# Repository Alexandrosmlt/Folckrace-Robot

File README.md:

# Folckrace Robot

## 1. Project Overview

#### This is an autonomous robot made for Folkrace (which is a robot competition centered around autonomous racing and steering skills). My design features 4 HS DC Motors paired with 5 ToF sensors, providing precise feedback in real time.

## 1.1 Why i am building this project

#### I am making this project to get real-life experience in developing complex systems and working with fast robotics controls. This project is great to help me improve my skills in putting together microcontrollers, motor drivers and sensors in order to create a autonomous and competitive robot.

## 2. Hardware and Design

### 2.1 3D Visualization

* **Front View**:

* **Rear View**:

* **Right View**:

* **Left View**:

* **Final View**:

### 2.2 Custom PCB 

* **PCB Top View**:

* **PCB Bottom View**:

* **PCB Schematic**:

### 2.3 Wiring Diagram

* **Wiring diagram**:

### 2.4 Pinout

#### 1. ToF Sensor Connections (5 Sensors)

>| Component | Function | ESP32 Pin |
>| :--- | :--- | :--- |
>| **I2C Bus** | Data Line (SDA) | **GPIO 21** |
>| **I2C Bus** | Clock Line (SCL) | **GPIO 22** |
>| ToF 1 | XSHUT Pin | **GPIO 33** |
>| ToF 2 | XSHUT Pin | **GPIO 32** |
>| ToF 3 | XSHUT Pin | **GPIO 27** |
>| ToF 4 | XSHUT Pin | **GPIO 26** |
>| ToF 5 | XSHUT Pin | **GPIO 25** |

#### Motor Driver (MDD3A)

>| MDD3A | Motor | Function | ESP32 Pin |
>| :--- | :--- | :--- | :--- |
>| M1A | Motor 1 | Forward Speed | **GPIO 19** |
>| M1B | Motor 1 | Reverse Speed | **GPIO 18** |
>| M2A | Motor 2 | Forward Speed | **GPIO 14** |
>| M2B | Motor 2 | Reverse Speed | **GPIO 13** |

#### 3. Total Used Pins

>| Type | Pin Numbers Used | Total |
>| :--- | :--- | :--- |
>| **Motor Driver (PWM)** | 19, 18, 14, 13 | 4 |
>| **I2C** | 21, 22 | 2 |
>| **ToF XSHUT** | 33, 32, 27, 26, 25 | 5 |
>| **TOTAL GPIO PINS USED** | | **11** |

## 3.Filmware

### Summury of [Code](/firmware/Folkrace.ino) (**NOT TESTED**):

#### 1.Setup: The ESP32 initializes Wi-Fi, OTA and I2C bus and configures all ToF's and assigns them a unique addresses.

#### 2.Imput: The main loop is reading the distance from all the sensors and compines them using weighted coefficients to calculate a single positional error.

#### 3.Control: It gets the error and feeds it in the PID controller, which calculates the correction needed to reduce the error to 0.

#### 4.Output: The correction finaly is applied to the motors using PWM signals.

## 3.1 Parts that require [3D printing](/STLs)

### Parts List:

* **[Front Bumper](/STLs/FrontBumper.stl)** (Quantity: 1)
* **[Rear Bumper](/STLs/RearBumper.stl)** (Quantity: 1)
* **[Side Bumpers](/STLs/SideBumper.stl)** (Quantity: 2)
* **[Motor Mounts](/STLs/MotorMount.stl)** (Quantity: 4)

<!-- ## 4. Bill of Materials (BOM)

| Item | Description | Quantity | Unit Price (€) | Total Price (€) | URL | Running Total (€ with Tax) |
| :--- | :--- | :--- | :--- | :--- | :--- | :--- |
| **DC Motors** | Drive Motors (6V 750RPM) | 4 | 16.00 | 64.00 | [https://www.jsumo.com](https://www.jsumo.com/core-dc-motor-6v-750rpm) | 64.00 |
| **Wheels** | Aluminum - Silicone Wheel Set | 2 | 15.50 | 31.00 | [https://www.jsumo.com](https://www.jsumo.com/jsumo-wheel-43x11mm-pair-soft-silicone) | 95.00 |
| **Microcontroller** | ESP32-DevKitC Development Board | 1 | 9.90 | 9.90 | [https://grobotronics.com](https://grobotronics.com/esp32-development-board-devkit-v1.html) | 104.90 |
| **Sensors** | VL53L0X Time-of-Flight (ToF) | 5 | 2.50 | 12.50 | [https://www.temu.com](https://www.temu.com/ul/kuiper/un9.html?subj=goods-un&_bg_fs=1&_p_rfs=1&_x_ns_prz_type=-1&_x_ns_sku_id=17594988870614&_x_ns_gid=601100157918115&mrk_rec=1&_x_ads_sub_channel=shopping&_p_rfs=1&_x_ns_prz_type=-1&_x_ns_sku_id=17594988870614&_x_ns_gid=601100157918115&mrk_rec=1&_x_ads_channel=google&_x_gmc_account=772005384&_x_login_type=Google&_x_ns_gg_lnk_type=adr&_x_ads_account=6217438245&_x_ads_set=22821535431&_x_ads_id=188619669811&_x_ads_creative_id=765746251322&_x_ns_source=g&_x_ns_gclid=Cj0KCQiA_8TJBhDNARIsAPX5qxS74_q9dhiTIvByNhVh8ld3DEGTAj0bWG-MgXinbjivbOwGYiuwb1QaAoYZEALw_wcB&_x_ns_placement=&_x_ns_match_type=&_x_ns_ad_position=&_x_ns_product_id=772005384-en-17594988870614&_x_ns_target=&_x_ns_devicemodel=&_x_ns_wbraid=CkEKCQiA3L_JBhDxARIwAHTwe8yn1e11-pFJWKQUheZHO7OYuOSTSn3rBLRa37kyxPEg2BQDQ9y3-UNT8ucWGgL0Rg&_x_ns_gbraid=0AAAAAo4mICHMEfKcJ0oOLcvVhMiL34SOE&_x_ns_targetid=pla-2625318551272&gad_source=1&gad_campaignid=22821535431&gbraid=0AAAAAo4mICHMEfKcJ0oOLcvVhMiL34SOE&gclid=Cj0KCQiA_8TJBhDNARIsAPX5qxS74_q9dhiTIvByNhVh8ld3DEGTAj0bWG-MgXinbjivbOwGYiuwb1QaAoYZEALw_wcB&is_back=1) | 117.40 |
| **Motor Driver** | Cytron MDD3A | 1 | 8.50 | 8.50 | [https://botland.store](https://botland.store/motor-drivers-modules/15819-cytron-mdd3a-dual-channel-16v-3a-motor-controller-5904422324841.html) | 125.90 |
| **Battery** | Battery Lithium 18650 | 2 | 5.80 | 11.60 | [https://grobotronics.com](https://grobotronics.com/battery-lithium-18650-3.6v-3200mah-lg-inr18650-mh1.html?srsltid=AfmBOorO9rHicRFxCaTsiuH0z1Nu5r90yx-F4EEb-n_gA3Yru7VgAYtV) | 137.50 |
| **Battery Holder** | Battery Holder 2×18650 with Plug 5.5×2.1 | 1 | 1 | 1 | [https://grobotronics.com](https://grobotronics.com/battery-holder-218650-with-plug-5-5x2-1.html) | 138.50 |
| **Pin Header** | Pin Header Female 1x6 2.54mm | 6 | 0.08 | 0.64 | [https://grobotronics.com](https://grobotronics.com/pin-header-1x6-female-2.54mm.html) | 139.14 |
| **Pin Header** | Pin Header 1x20 Female 2.54mm| 2 | 0.25 | 0.50 | [https://grobotronics.com](https://grobotronics.com/pin-header-1x20-female-2.54mm.html) | 139.64 |
| **PCB Manufacturing** | PCBWay | 5 | $47.78 | $75.75 | [https://www.pcbway.com](https://www.pcbway.com/QuickOrderOnline.aspx) | 215.39 |
 -->

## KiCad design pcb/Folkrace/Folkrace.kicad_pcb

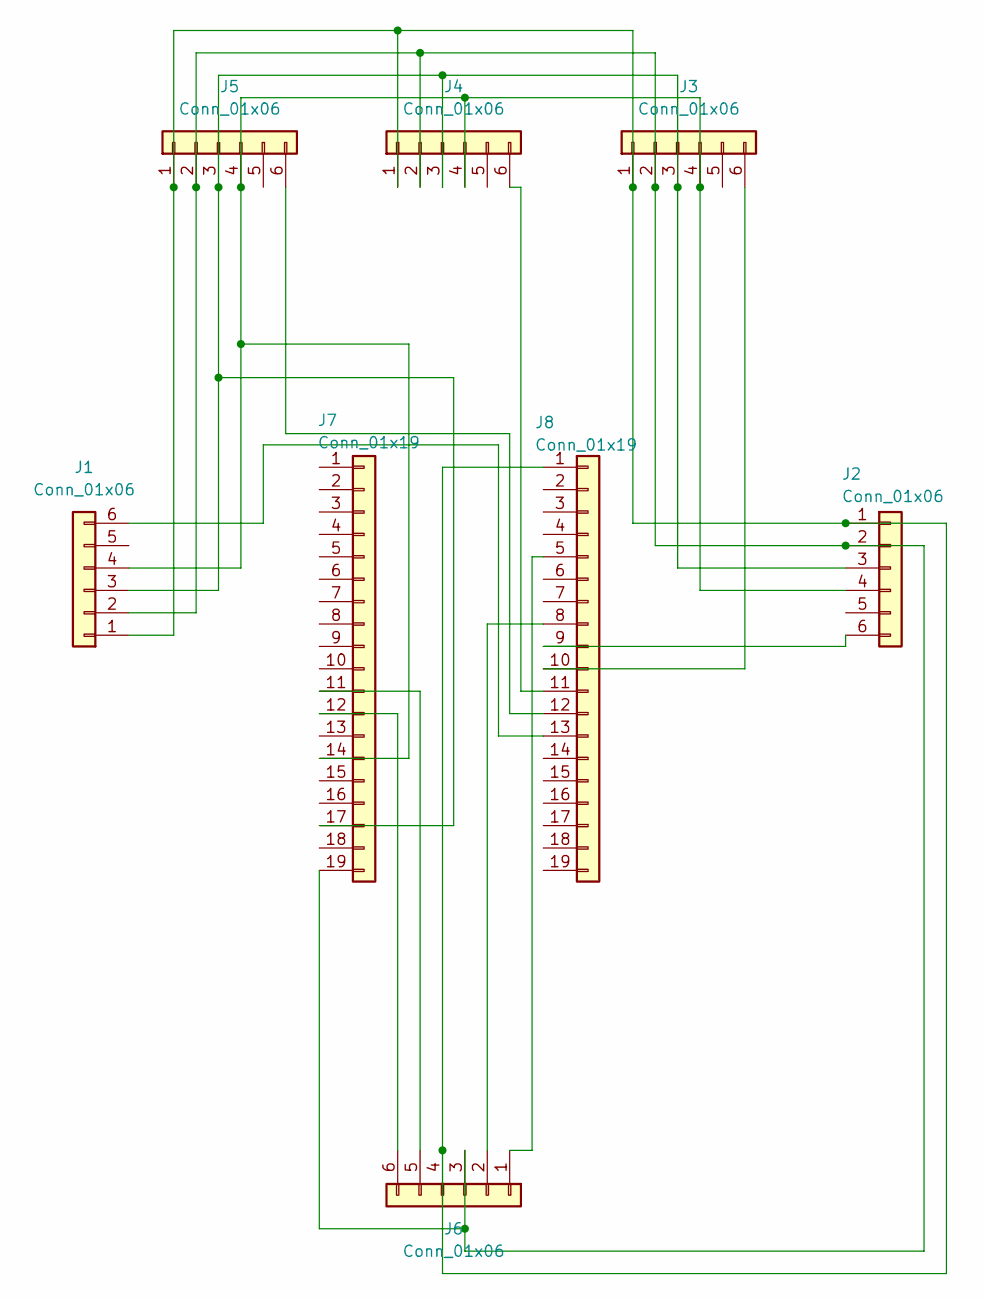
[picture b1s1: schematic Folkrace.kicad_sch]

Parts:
J1, J2, J3, J4, J5: Conn_01x06; PinSocket_1x06_P2.54mm_Horizontal
J6: Conn_01x06; PinSocket_1x06_P2.54mm_Vertical
J7, J8: Conn_01x19; PinSocket_1x19_P2.54mm_Vertical

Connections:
unnamed: J1.1, J2.1, J3.1, J4.1, J5.1, J6.4, J8.1
unnamed: J1.2, J2.2, J3.2, J4.2, J5.2, J6.3, J7.19
unnamed: J1.3, J2.3, J3.3, J4.3, J5.3, J7.17
unnamed: J1.4, J2.4, J3.4, J4.4, J5.4, J7.14
unnamed: J1.6, J8.13
unnamed: J2.6, J8.9
unnamed: J3.6, J8.10
unnamed: J4.6, J8.11
unnamed: J5.6, J8.12
unnamed: J6.1, J8.5
unnamed: J6.2, J8.8
unnamed: J6.5, J7.11
unnamed: J6.6, J7.12

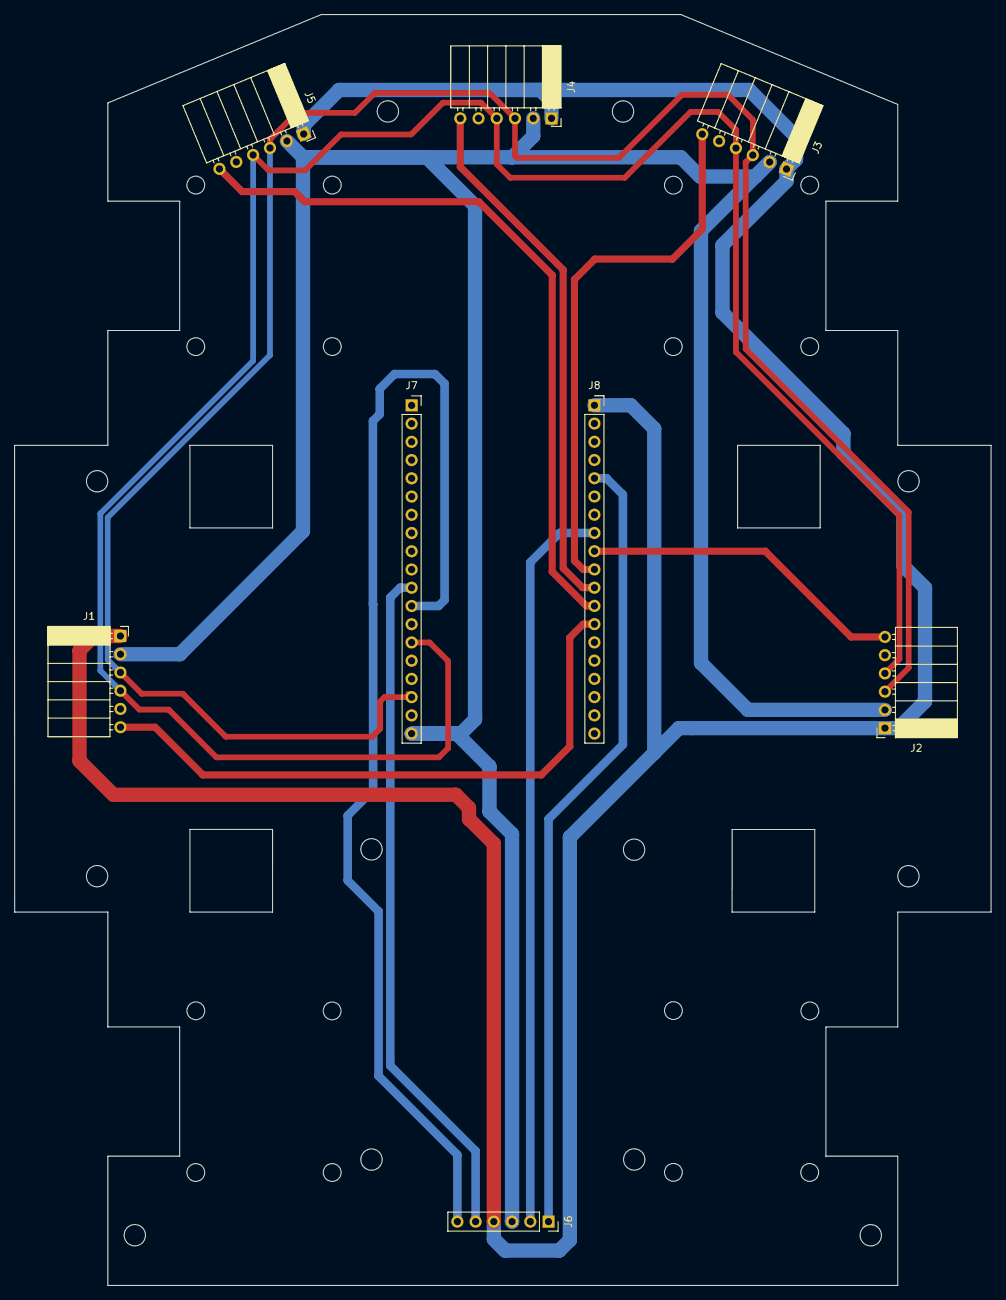
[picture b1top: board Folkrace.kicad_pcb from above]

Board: 2 copper layers, 136.0 x 177.0 mm, 8 parts (0 on the bottom side), 13 nets.

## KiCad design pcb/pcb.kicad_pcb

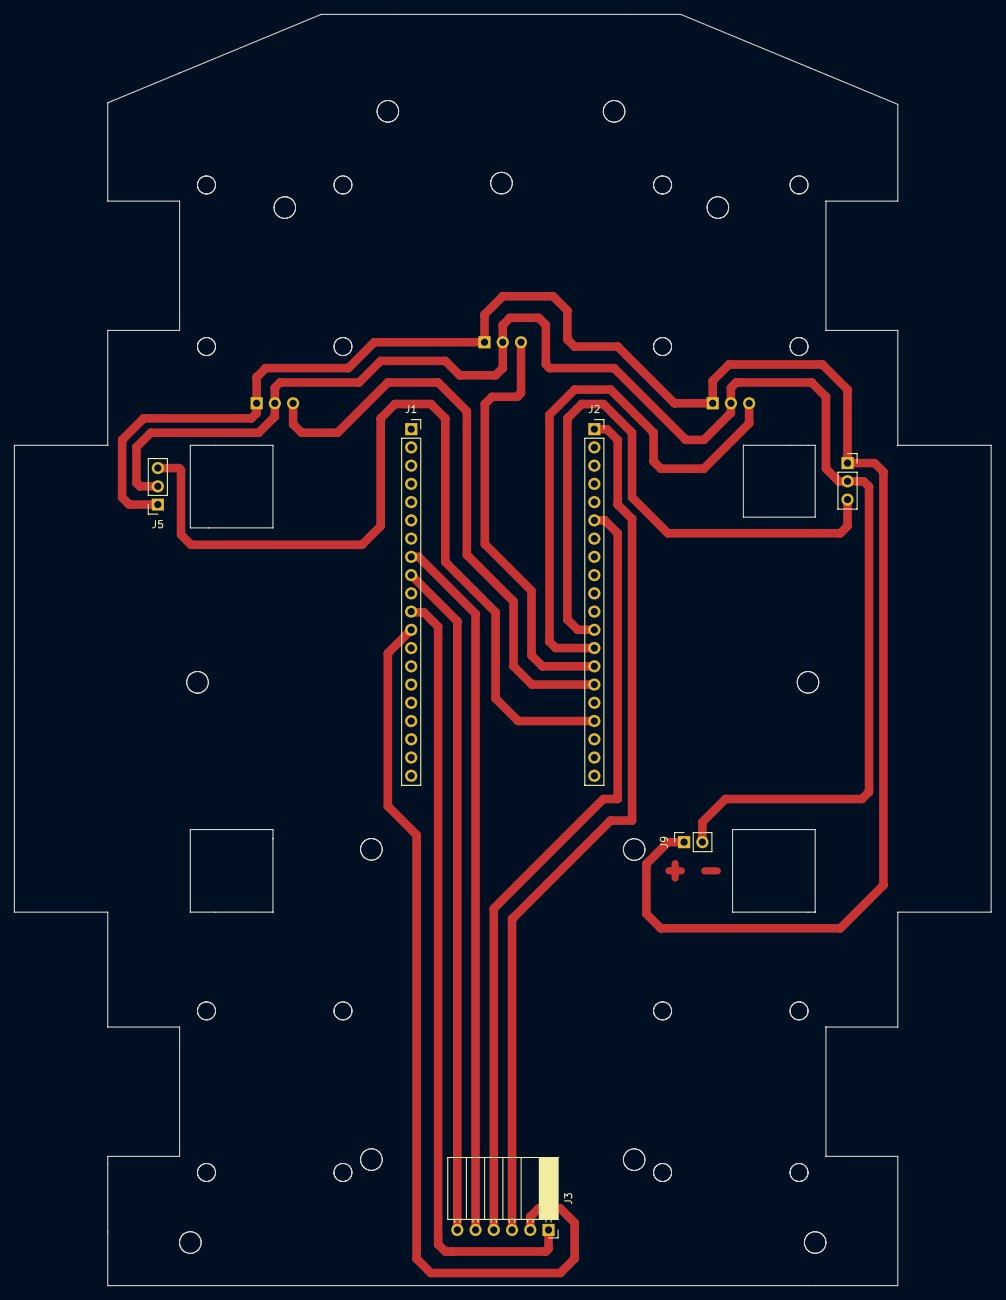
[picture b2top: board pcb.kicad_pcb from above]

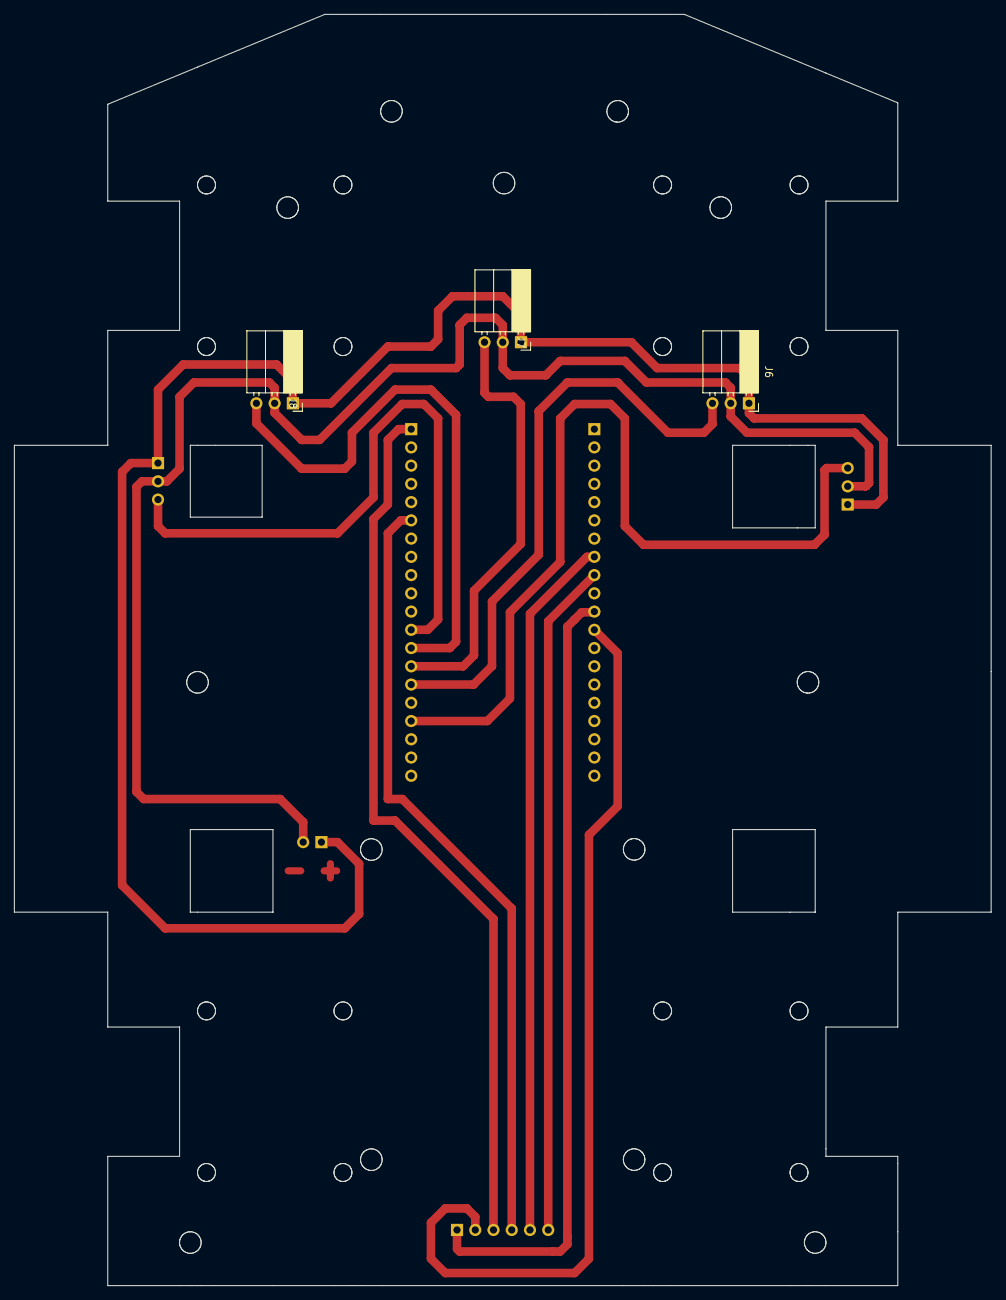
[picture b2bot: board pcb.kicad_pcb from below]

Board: 2 copper layers, 136.0 x 177.0 mm, 9 parts (3 on the bottom side), 13 nets.

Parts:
J1, J2: Conn_01x20; PinSocket_1x20_P2.54mm_Vertical
J3: Conn_01x06; PinSocket_1x06_P2.54mm_Horizontal
J4, J5: Conn_01x03; PinSocket_1x03_P2.54mm_Vertical
J6, J7, J8: Conn_01x03; PinSocket_1x03_P2.54mm_Horizontal
J9: Conn_01x02; PinSocket_1x02_P2.54mm_Vertical

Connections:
unnamed: J1.8, J3.5
unnamed: J1.9, J3.6
unnamed: J1.11, J3.1
unnamed: J1.12, J3.2
unnamed: J2.1, J3.3
unnamed: J2.6, J3.4
unnamed: J2.12, J4.3
unnamed: J2.13, J8.3
unnamed: J2.14, J7.3
unnamed: J2.15, J6.3
unnamed: J2.17, J5.3
unnamed: J4.1, J5.1, J6.1, J7.1, J8.1, J9.1
unnamed: J4.2, J5.2, J6.2, J7.2, J8.2, J9.2

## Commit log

2025-12-04 Create cad
2025-12-04 Create pcb
2025-12-04 Create Firmware
2025-12-04 new folders and Made the VL53L0X 3d model
2025-12-04 Added a Photo of the 3d ToF sensor
2025-12-04 Added the .stl of ToF in 3d
2025-12-04 Updated JOURNAL.md
2025-12-04 README update
    Added a Bill of Materials section on README
2025-12-04 README update
    Added prices to the compoments
2025-12-04 New components
    Updated the Bill of Materials section with new items and prices.
2025-12-05 Made the Motors and motor driver
2025-12-05 Made 3d models for esp32 and MDD3A
2025-12-05 Made the first version of the motor mount
2025-12-05 New Motor Mount , Updated README.md, added STLs folder for the future
2025-12-05 fixed some falses
2025-12-06 V1 of the base
2025-12-06 V1 of the Front Bumper
2025-12-06 Base V1
2025-12-06 Front Bumper .stl and .FCStd
2025-12-08 Updayed
    Updated project description and clarified components.
2025-12-08 added .gitIn\gnore
2025-12-08 Made .gitignore
2025-12-08 Removed .gitignore
2025-12-08 Made holes to base for front and side bumpers
2025-12-08 Made Side Bumper for right and left
2025-12-08 Updated base for MDD3A Motor Driver
2025-12-08 Updated the name of the file
2025-12-09 Updated Base for the folkrace robot
2025-12-09 MotorMount Photo
2025-12-09 Made Back bumper for the back of the robot
2025-12-09 added .stl of BackBumper
2025-12-09 base, and mounts update
2025-12-09 Updated Rear Bumper
2025-12-09 Final 3D Model
2025-12-09 Added Final Photos
2025-12-12 Remove empty line in JOURNAL.md
2025-12-13 Made the pcb scematic
2025-12-13 updated PCB
2025-12-14 New Base.svg
2025-12-15 Updated Base
2025-12-15 Made svg files
2025-12-15 Photo of the svg base
2025-12-16 updated parts
2025-12-16 updated GUIDE.md
2025-12-16 Untested code
2025-12-16 New Photos
2025-12-17 Ready for print
2025-12-17 Added all compoments
2025-12-29 New top cover
2025-12-29 Updated photos
